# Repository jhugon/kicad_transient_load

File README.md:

# KiCad Transient Load

For step-response testing power supplies.

A resistor and MOSFET switch hooked up to a BNC jack. Hook up a signal
generator to the BNC jack and the other leads to the power supply device under
test.

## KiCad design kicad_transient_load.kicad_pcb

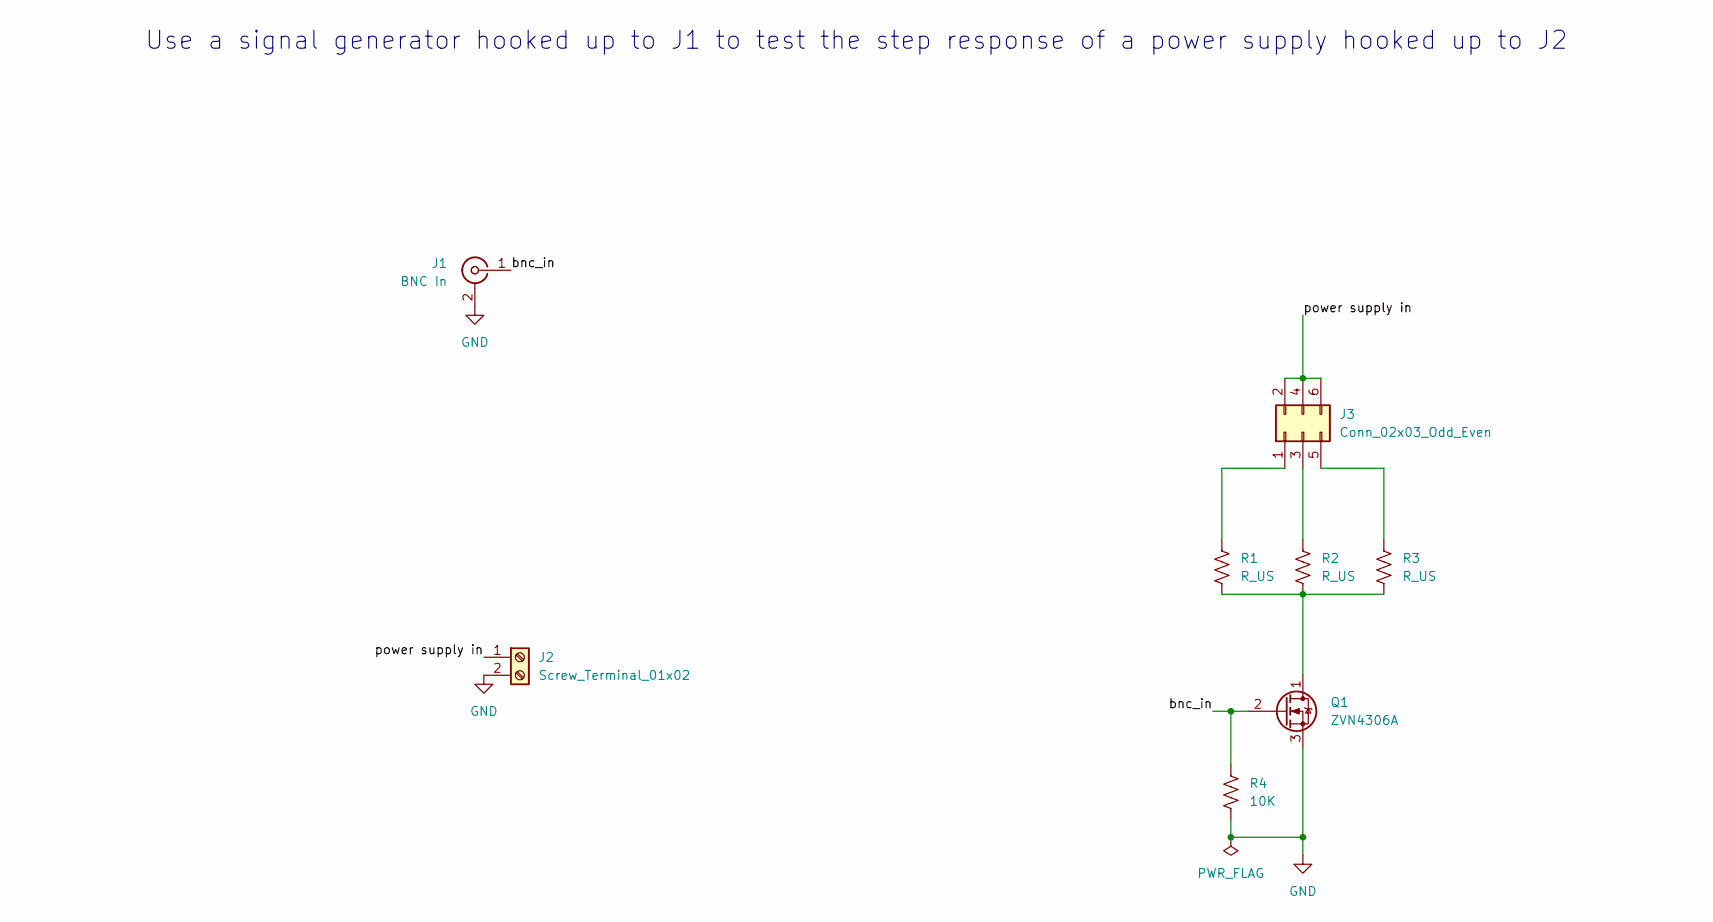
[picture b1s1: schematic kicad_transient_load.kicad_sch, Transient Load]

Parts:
J1: BNC In; BNC_TE-Connectivity_1-1337445-0; MFR Part No 1-1337445-0
J2: Screw_Terminal_01x02; TerminalBlock_TE_282834-2_1x02_P2.54mm_Horizontal; MFR Part No 282834-2
J3: Conn_02x03_Odd_Even; PinHeader_2x03_P2.54mm_Vertical; MFR Part No 9-146261-0
Q1: ZVN4306A; TO-92_Inline; MFR Part No ZVN4306A
R1, R2, R3: R_US; R_Axial_DIN0918_L18.0mm_D9.0mm_P22.86mm_Horizontal
R4: 10K; R_Axial_DIN0207_L6.3mm_D2.5mm_P7.62mm_Horizontal; MFR Part No MF1/4LCT52R103J

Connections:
/bnc_in: J1.1 (In), Q1.2 (G), R4.2
/power supply in: J2.1, J3.2, J3.4, J3.6
GND: J1.2 (Ext), J2.2, Q1.3 (S), R4.1
unnamed: J3.1, R1.1
unnamed: J3.3, R2.1
unnamed: J3.5, R3.1
unnamed: Q1.1 (D), R1.2, R2.2, R3.2

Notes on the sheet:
Use a signal generator hooked up to J1 to test the step response of a power supply hooked up to J2

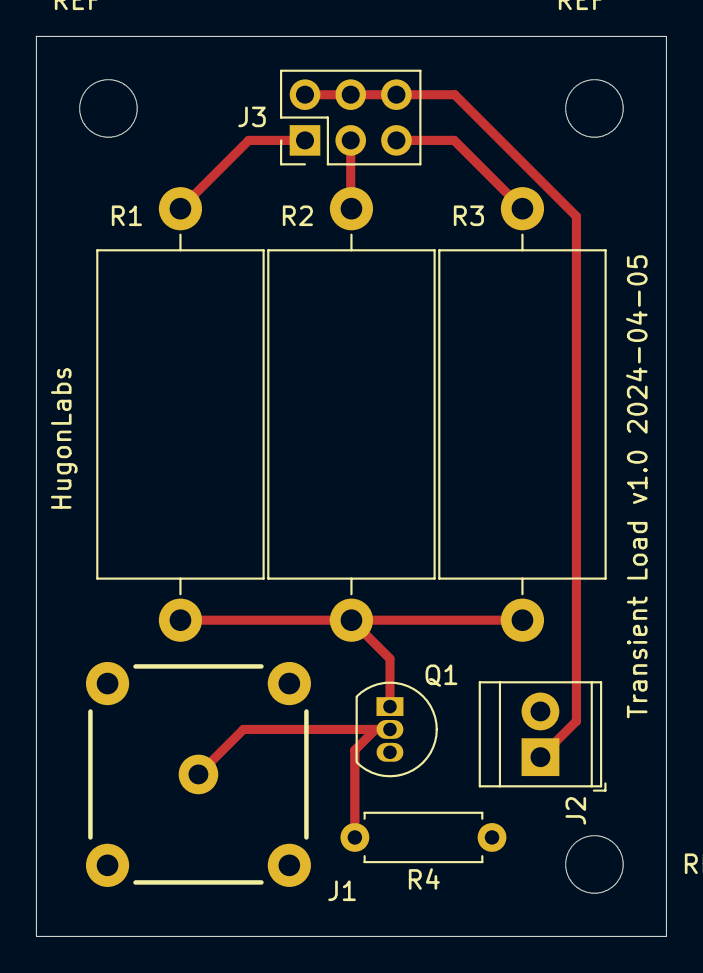
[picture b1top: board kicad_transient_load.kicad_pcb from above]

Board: 2 copper layers, 35.0 x 50.0 mm, 8 parts (0 on the bottom side), 7 nets.

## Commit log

2024-04-03 Initial commit--few things on sch
2024-04-03 added README.md
2024-04-03 schematic laid out
2024-04-03 Working on BNC footprint
2024-04-05 finished footprint for BNC connector and added
2024-04-05 added BOM
2024-04-05 placed components, widended silk on BNC connector
2024-04-05 route all but gnd plane, add screw holes and board outline
2024-04-05 finished pcb
2024-04-05 Add .pdfs for sch and pcb as well as renders that show in readme
